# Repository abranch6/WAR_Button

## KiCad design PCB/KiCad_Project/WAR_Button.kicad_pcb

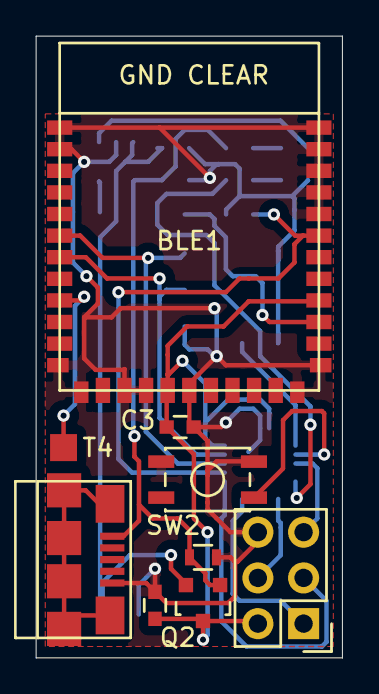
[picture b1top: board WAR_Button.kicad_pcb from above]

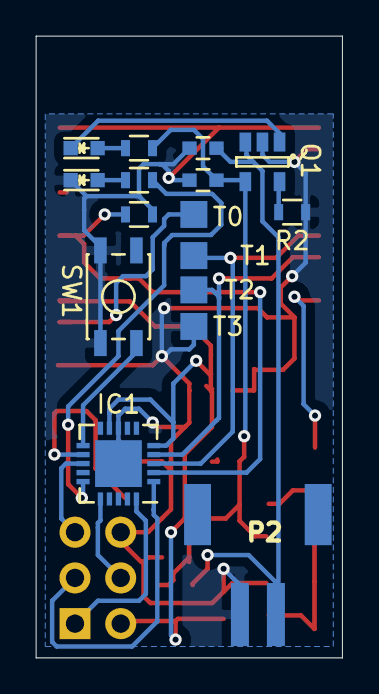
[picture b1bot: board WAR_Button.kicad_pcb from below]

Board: 2 copper layers, 17.0 x 34.5 mm, 25 parts (16 on the bottom side), 20 nets.

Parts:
BLE1: BC118; bc118
C1, C2: 4.7uF; C_0603
C3: 10nF; C_0603
C4: 1uF; C_0603
D1, D2: LED; LED-0603
IC1: ATTINY84A-M; qfn20
P1: USB_OTG; USB_Micro-B
P2: BATT; JST_2
P3: HEADER; Pin_Header_Straight_2x03
Q1: MCP73831; SOT-23-5
Q2: NTR2101PT1G; SOT-23
R1, R3: LED_R; R_0603
R2: PROG; R_0603
R4, R5: 100K; R_0603
SW1, SW2: SW_PUSH; SW_SPST_EVQP2
T0: T0; Measurement_Point_Square-SMD-Pad_Small
T1: T1; Measurement_Point_Square-SMD-Pad_Small
T2: T2; Measurement_Point_Square-SMD-Pad_Small
T3: T3; Measurement_Point_Square-SMD-Pad_Small
T4: T4; Measurement_Point_Square-SMD-Pad_Small

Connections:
BATT_VCC: C2.2, P2.2, Q1.3, Q2.2
BLED1: BLE1.9, T4.1
BLED2: BLE1.26, T0.1
BLE_RX: BLE1.7, IC1.4, T2.1
BLE_TX: BLE1.6, IC1.3, T1.1
LOAD_VCC: BLE1.17, BLE1.27, C3.2, C4.2, IC1.5, IC1.9, P3.2, Q2.3
unnamed: D1.1, Q1.1
unnamed: D1.2, R1.2
unnamed: D2.2, R3.1
unnamed: IC1.11, SW1.1
unnamed: IC1.12, SW2.1
unnamed: IC1.15, R3.2
unnamed: Q1.5, R2.1
P1: IC1.1, P3.3
P2: IC1.20, P3.1
P3: IC1.16, P3.4
P4: IC1.13, P3.5
PROG_GND: BLE1.1, BLE1.2, BLE1.12, BLE1.13, BLE1.15, BLE1.16, BLE1.18, BLE1.23, BLE1.24, BLE1.31, BLE1.32, BLE1.33, BLE1.34, BLE1.35, C1.2, C2.1, C3.1, C4.1, D2.1, IC1.8, IC1.21, P1.5, P2.1, P3.6, Q1.2, R2.2, R4.2, R5.1, SW1.2, SW2.2, T3.1
USB_VCC: C1.1, P1.1, Q1.4, Q2.1, R1.1, R5.2
WAKE: BLE1.30, IC1.2, R4.1

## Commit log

2015-09-23 Added BLE2 Mate Library
2015-09-23 Added test sketch
2015-09-24 --Updated test sketch
2015-09-25 --Added more test sketches
2015-10-14 Added PCB design for KiCad
2015-10-14 WAR Button main arduino code
2015-10-15 Updated Schematic
2015-10-19 -Updated pin numbers to match with schematic
2015-10-25 Changed to DMT instead of Sleep
2015-10-28 Added footprints
2015-10-29 Updated Button code Updated Schematic
2015-11-08 -Finished PCB Design
2015-11-10 Initial commit of phone app
2015-11-12 Added MOSFET
2015-11-13 Added GERBER and Drill files
2015-11-26 Second Commit
2015-11-29 Fixed stuff
2015-11-29 Added timeouts to button presses
2015-12-01 merging all the stuff
2015-12-01 start merging together from here
2015-12-01 version 1
2015-12-01 version1
2015-12-01 deleted legacy
2015-12-01 Verion 1
2015-12-01 integrating code, added pairing screen
2015-12-02 Added device communication
2015-12-02 updated arduino sketch
2015-12-02 made changes to contact
2015-12-02 initial delete functionality
2015-12-02 stuff
2015-12-02 refined the button press
2015-12-02 Fixed button change issue cleaned up device code
2015-12-02 Cleaned up arduino code added longer scan time for android
2015-12-02 Added component list
2015-12-03 updated arduino code
2015-12-04 Updated timeouts
2015-12-04 Added javadoc comments and removed extra stuff from the repo
2015-12-04 removed extra stuff from the repo
2015-12-04 Added CONTENTS text file Clarified the schematic for the device.
